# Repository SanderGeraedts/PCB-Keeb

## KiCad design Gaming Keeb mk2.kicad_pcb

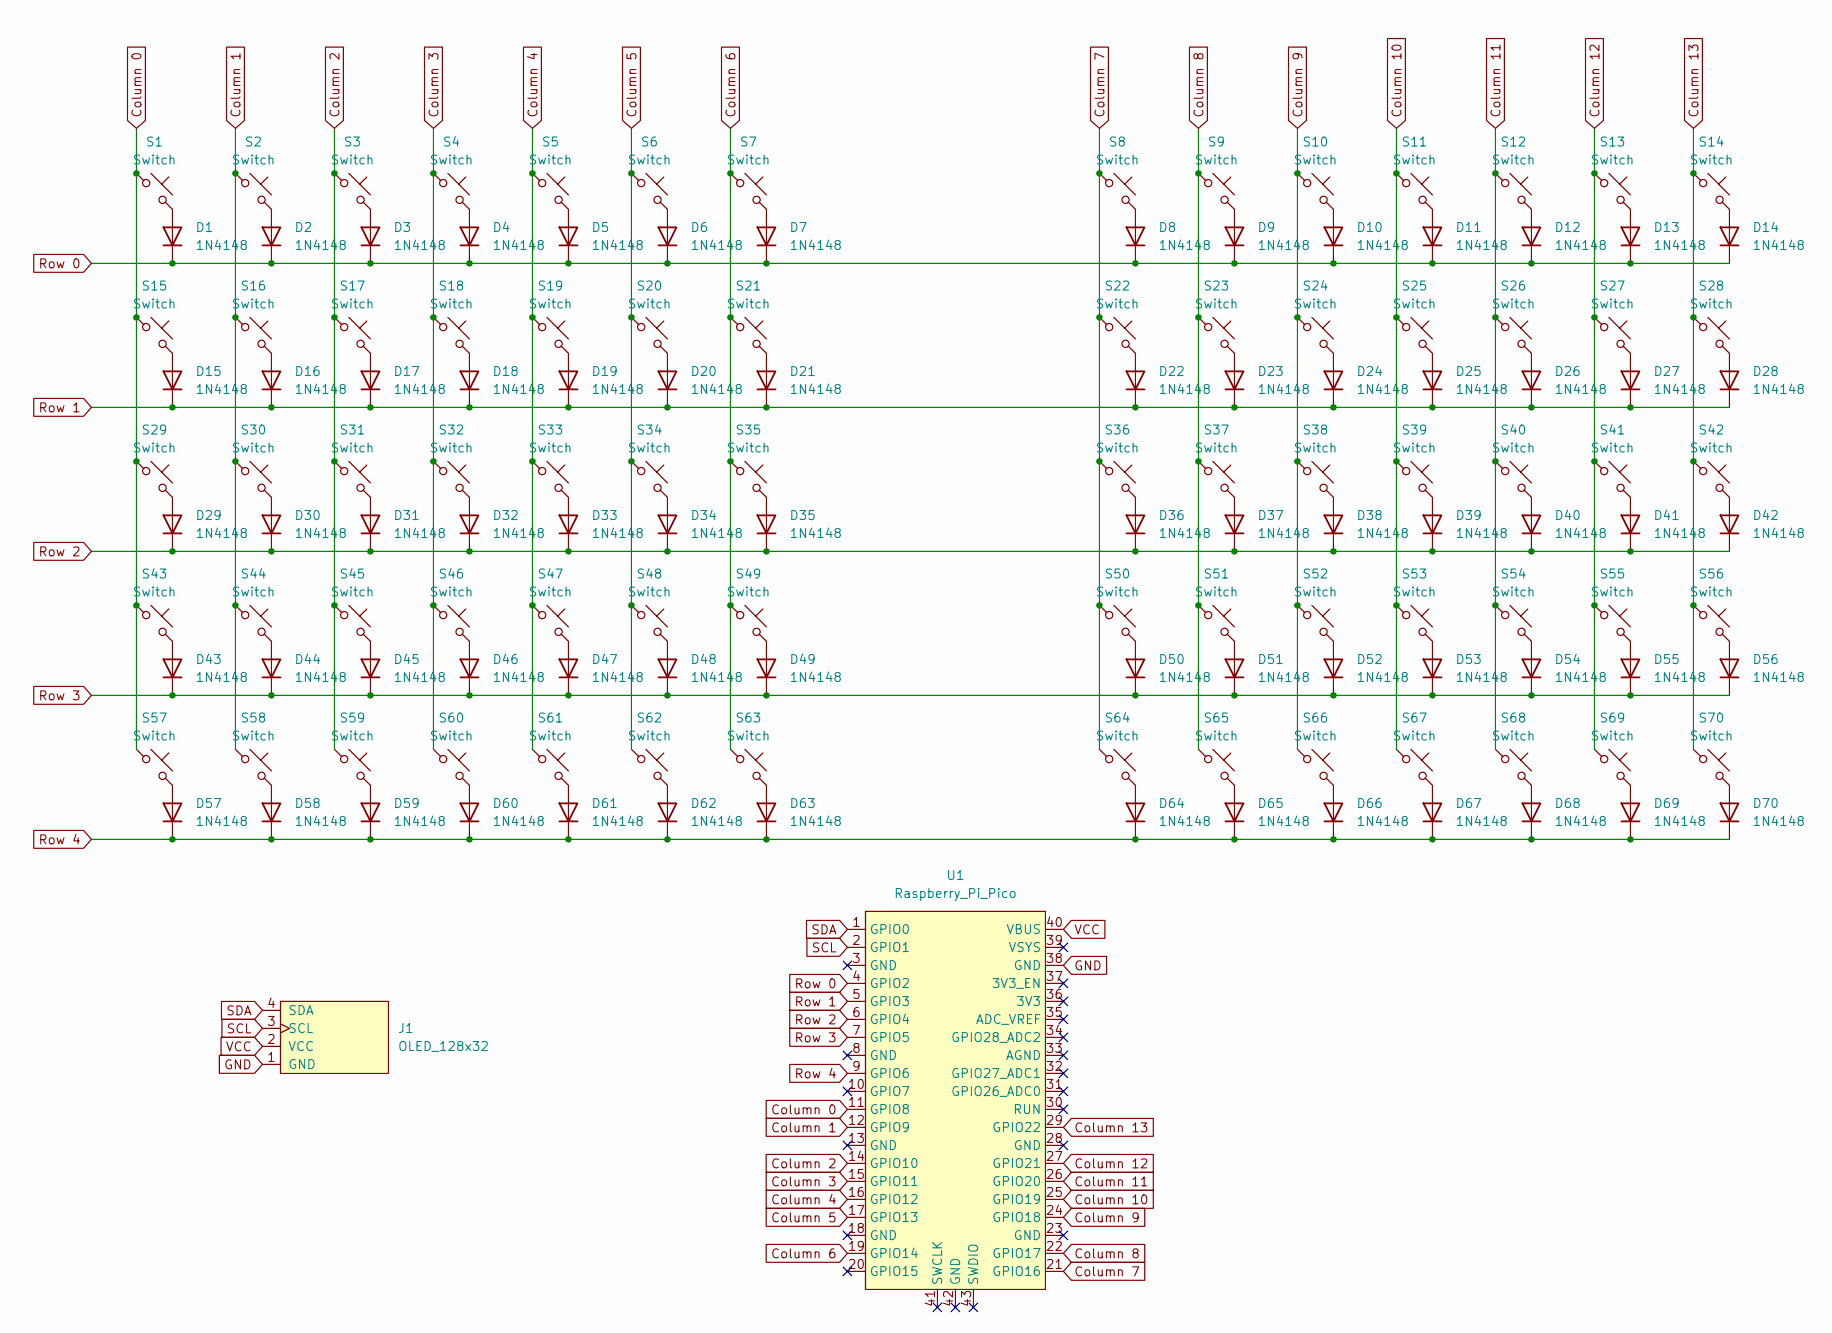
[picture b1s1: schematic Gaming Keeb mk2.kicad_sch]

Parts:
D1, D2, D3, D4, D5, D6, D7, D8, D9, D10, D11, D12, D13, D14, D15, D16, D17, D18, D19, D20, D21, D22, D23, D24, D25, D26, D27, D28, D29, D30, D31, D32, D33, D34, D35, D36, D37, D38, D39, D40, D41, D42, D43, D44, D45, D46, D47, D48, D49, D50, D51, D52, D53, D54, D55, D56, D57, D58, D59, D60, D61, D62, D63, D64, D65, D66, D67, D68, D69, D70: 1N4148; Diode_DO-35
J1: OLED_128x32
S1, S2, S3, S4, S5, S6, S7, S8, S9, S10, S11, S12, S13, S14, S15, S16, S17, S18, S19, S20, S21, S22, S23, S24, S25, S26, S27, S28, S29, S30, S31, S32, S33, S34, S35, S36, S37, S38, S39, S40, S41, S42, S43, S44, S45, S46, S47, S48, S49, S50, S51, S52, S53, S54, S55, S56, S57, S58, S59, S60, S61, S62, S63, S64, S65, S66, S67, S68, S69, S70: Switch; Hotswap_MX_1.00u
U1: Raspberry_Pi_Pico

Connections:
Column 0: S1.1, S15.1, S29.1, S43.1, S57.1, U1.11 (GPIO8)
Column 1: S2.1, S16.1, S30.1, S44.1, S58.1, U1.12 (GPIO9)
Column 2: S3.1, S17.1, S31.1, S45.1, S59.1, U1.14 (GPIO10)
Column 3: S4.1, S18.1, S32.1, S46.1, S60.1, U1.15 (GPIO11)
Column 4: S5.1, S19.1, S33.1, S47.1, S61.1, U1.16 (GPIO12)
Column 5: S6.1, S20.1, S34.1, S48.1, S62.1, U1.17 (GPIO13)
Column 6: S7.1, S21.1, S35.1, S49.1, S63.1, U1.19 (GPIO14)
Column 7: S8.1, S22.1, S36.1, S50.1, S64.1, U1.21 (GPIO16)
Column 8: S9.1, S23.1, S37.1, S51.1, S65.1, U1.22 (GPIO17)
Column 9: S10.1, S24.1, S38.1, S52.1, S66.1, U1.24 (GPIO18)
Column 10: S11.1, S25.1, S39.1, S53.1, S67.1, U1.25 (GPIO19)
Column 11: S12.1, S26.1, S40.1, S54.1, S68.1, U1.26 (GPIO20)
Column 12: S13.1, S27.1, S41.1, S55.1, S69.1, U1.27 (GPIO21)
Column 13: S14.1, S28.1, S42.1, S56.1, S70.1, U1.29 (GPIO22)
GND: J1.1 (GND), U1.38 (GND)
unnamed: D1.2 (A), S1.2
unnamed: D2.2 (A), S2.2
unnamed: D3.2 (A), S3.2
unnamed: D4.2 (A), S4.2
unnamed: D5.2 (A), S5.2
unnamed: D6.2 (A), S6.2
unnamed: D7.2 (A), S7.2
unnamed: D8.2 (A), S8.2
unnamed: D9.2 (A), S9.2
unnamed: D10.2 (A), S10.2
unnamed: D11.2 (A), S11.2
unnamed: D12.2 (A), S12.2
unnamed: D13.2 (A), S13.2
unnamed: D14.2 (A), S14.2
unnamed: D15.2 (A), S15.2
unnamed: D16.2 (A), S16.2
unnamed: D17.2 (A), S17.2
unnamed: D18.2 (A), S18.2
unnamed: D19.2 (A), S19.2
unnamed: D20.2 (A), S20.2
unnamed: D21.2 (A), S21.2
unnamed: D22.2 (A), S22.2
unnamed: D23.2 (A), S23.2
unnamed: D24.2 (A), S24.2
unnamed: D25.2 (A), S25.2
unnamed: D26.2 (A), S26.2
unnamed: D27.2 (A), S27.2
unnamed: D28.2 (A), S28.2
unnamed: D29.2 (A), S29.2
unnamed: D30.2 (A), S30.2
unnamed: D31.2 (A), S31.2
unnamed: D32.2 (A), S32.2
unnamed: D33.2 (A), S33.2
unnamed: D34.2 (A), S34.2
unnamed: D35.2 (A), S35.2
unnamed: D36.2 (A), S36.2
unnamed: D37.2 (A), S37.2
unnamed: D38.2 (A), S38.2
unnamed: D39.2 (A), S39.2
unnamed: D40.2 (A), S40.2
unnamed: D41.2 (A), S41.2
unnamed: D42.2 (A), S42.2
unnamed: D43.2 (A), S43.2
unnamed: D44.2 (A), S44.2
unnamed: D45.2 (A), S45.2
unnamed: D46.2 (A), S46.2
unnamed: D47.2 (A), S47.2
unnamed: D48.2 (A), S48.2
unnamed: D49.2 (A), S49.2
unnamed: D50.2 (A), S50.2
unnamed: D51.2 (A), S51.2
unnamed: D52.2 (A), S52.2
unnamed: D53.2 (A), S53.2
unnamed: D54.2 (A), S54.2
unnamed: D55.2 (A), S55.2
unnamed: D56.2 (A), S56.2
unnamed: D57.2 (A), S57.2
unnamed: D58.2 (A), S58.2
unnamed: D59.2 (A), S59.2
unnamed: D60.2 (A), S60.2
unnamed: D61.2 (A), S61.2
unnamed: D62.2 (A), S62.2
unnamed: D63.2 (A), S63.2
unnamed: D64.2 (A), S64.2
unnamed: D65.2 (A), S65.2
unnamed: D66.2 (A), S66.2
unnamed: D67.2 (A), S67.2
unnamed: D68.2 (A), S68.2
unnamed: D69.2 (A), S69.2
unnamed: D70.2 (A), S70.2
Row 0: D1.1 (K), D2.1 (K), D3.1 (K), D4.1 (K), D5.1 (K), D6.1 (K), D7.1 (K), D8.1 (K), D9.1 (K), D10.1 (K), D11.1 (K), D12.1 (K), D13.1 (K), D14.1 (K), U1.4 (GPIO2)
Row 1: D15.1 (K), D16.1 (K), D17.1 (K), D18.1 (K), D19.1 (K), D20.1 (K), D21.1 (K), D22.1 (K), D23.1 (K), D24.1 (K), D25.1 (K), D26.1 (K), D27.1 (K), D28.1 (K), U1.5 (GPIO3)
Row 2: D29.1 (K), D30.1 (K), D31.1 (K), D32.1 (K), D33.1 (K), D34.1 (K), D35.1 (K), D36.1 (K), D37.1 (K), D38.1 (K), D39.1 (K), D40.1 (K), D41.1 (K), D42.1 (K), U1.6 (GPIO4)
Row 3: D43.1 (K), D44.1 (K), D45.1 (K), D46.1 (K), D47.1 (K), D48.1 (K), D49.1 (K), D50.1 (K), D51.1 (K), D52.1 (K), D53.1 (K), D54.1 (K), D55.1 (K), D56.1 (K), U1.7 (GPIO5)
Row 4: D57.1 (K), D58.1 (K), D59.1 (K), D60.1 (K), D61.1 (K), D62.1 (K), D63.1 (K), D64.1 (K), D65.1 (K), D66.1 (K), D67.1 (K), D68.1 (K), D69.1 (K), D70.1 (K), U1.9 (GPIO6)
SCL: J1.3 (SCL), U1.2 (GPIO1)
SDA: J1.4 (SDA), U1.1 (GPIO0)
VCC: J1.2 (VCC), U1.40 (VBUS)

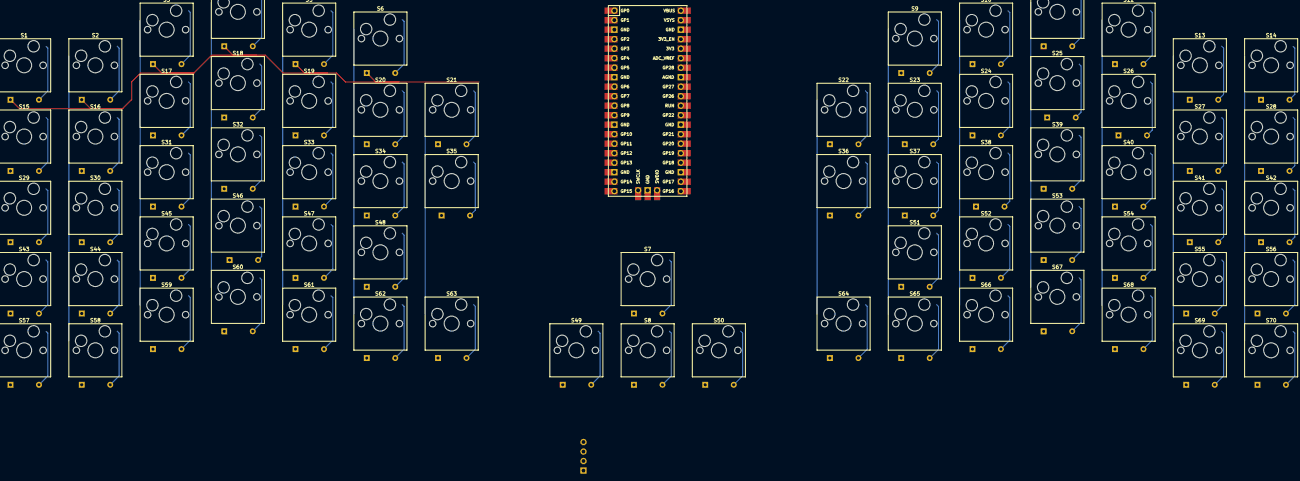
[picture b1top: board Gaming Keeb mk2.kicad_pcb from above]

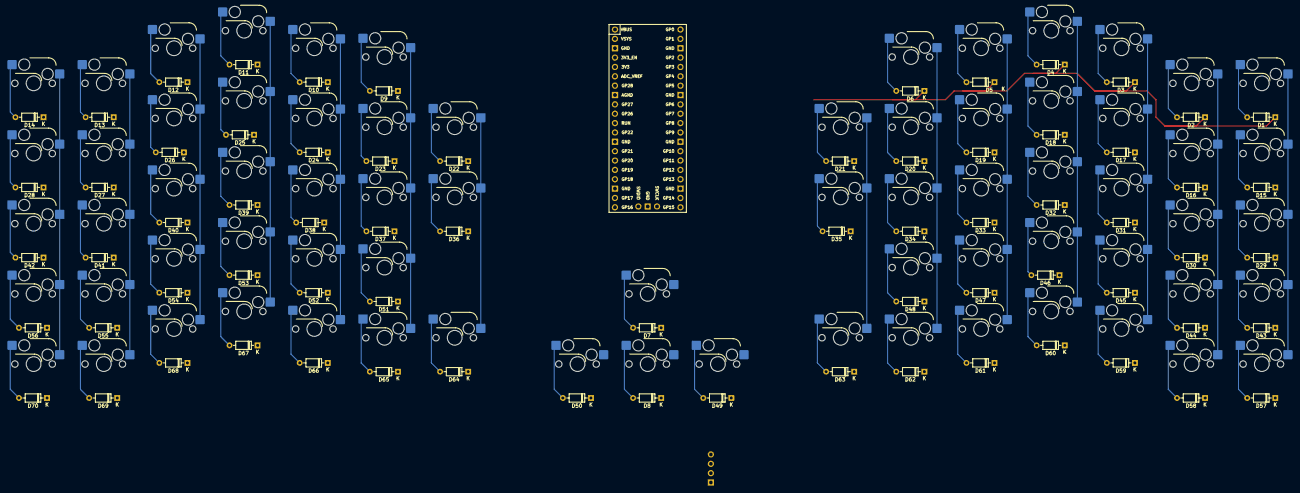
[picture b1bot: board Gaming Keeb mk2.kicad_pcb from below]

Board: 2 copper layers, 142 parts (70 on the bottom side), 93 nets.

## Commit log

2023-09-12 v.0.1 of Mk2
